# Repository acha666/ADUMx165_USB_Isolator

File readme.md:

# ADUMx165 USB Isolator

[Chinese Document / 中文文档](./readme.zh.md) | English Document

This is a USB 2.0 High-Speed (480Mbps) isolation module with an onboard 1-to-4 USB HUB, a 1A isolated DC-DC power supply, and support for external auxiliary power input with automatic switching between the two.

## Project Status

- [x] Schematic Design
- [x] PCB Design
- [x] PCB Fabrication
- [x] PCB Validation

## Device Overview

- **[ADUM3165](https://www.analog.com/en/products/adum3165.html)/[ADUM4165](https://www.analog.com/en/products/adum4165.html) USB Isolator**: Provides 480Mbps USB isolation with 3.75kV/5.7kV RMS isolation voltage. Pin-to-pin compatible.
- **[SN6505A](https://www.ti.com/product/SN6505A)/[B](https://www.ti.com/product/SN6505B) Transformer Driver**: An isolated DC-DC power controller powered directly from the upstream USB port. The two variants differ in switching frequency.
- **[DA2303-AL](https://www.coilcraft.com/en-us/products/transformers/power-transformers/isolation/da230x/da2303-al) Transformer**: 1:1.5 SMT transformer.
- **[TPS2116](https://www.ti.com/product/TPS2116) Power Multiplexer**: Prioritizes 5V auxiliary power from the downstream port. When unavailable, it automatically switches to the onboard isolated DC-DC power supply.
- **[TLV76701](https://www.ti.com/product/TLV767) LDO**: Regulates the output of the SN6505.
- **[CH334P](https://www.wch-ic.com/products/CH334.html) USB Hub**: A simple USB 2.0 1-to-4 HUB chip.

## Basic PCB Parameters

| Parameter               | Value                  |
|:-----------------------:|:----------------------:|
| **Dimensions**           | 50.00mm x 36.50mm     |
| **Shape**                | Rounded Rectangle, r=1.50mm |
| **Finished Thickness**   | 1.60mm                |
| **Copper Layers**        | 4                     |
| **Minimum Trace Width**  | 0.12mm                |
| **Minimum Trace Space**  | 0.12mm                |
| **Minimum Via Hole Diameter** | 0.20mm         |
| **Minimum Non-plated Hole Diameter** | >1.00mm |
| **Minimum Via Outer Diameter** | 0.45mm         |
| **Minimum Via Inner Diameter** | 0.20mm         |
| **Minimum Plated Slot Width** | 0.60mm          |
| **Minimum Non-plated Slot Width** | None        |
| **Special Manufacturing Processes** | Impedance Control |

## Impedance Control Parameters

### Differential Impedance 1

| Usage           | USB 2.0 Signals          |
|:---------------:|:------------------------:|
| **Signal Layers** | L1, L4                 |
| **Impedance**     | 90Ω                    |
| **Bottom Reference Layers** | L2, L3       |
| **Top Reference Layer** | None             |

| Current Design Parameters | Value            |
|:-------------------------:|:----------------:|
| **Trace Width**            | 0.12mm          |
| **Trace Spacing**          | 0.12mm          |
| **Copper Thickness**       | 1oz/0.5oz       |
| **Applicable PCB Stackup** | JLCPCB JLC04161H-3313 |

## Project Description

This project was designed using KiCad 8.06.

GitHub Action CI/CD is deployed, which automatically performs DRC checks and generates manufacturing files (e.g., Gerber files) with each commit.

Manufacturing files are available on the [Release Page](https://github.com/acha666/ADUMx165_USB_Isolator/releases) or the [Workflow](https://github.com/acha666/ADUMx165_USB_Isolator/actions/workflows/kicad-ci.yml).

### Power Design

The module includes a 1A onboard isolated DC-DC power supply and supports external auxiliary power input with automatic switching. The onboard LED indicates that the isolated-side 5V is provided by the onboard DC-DC power supply.

- When using a 5V external auxiliary power supply, the output ports prioritize this external power. The total output capacity depends on the external power supply. Each port is equipped with a self-recovering fuse, limiting current to 500mA.
- When no external power is connected, the onboard isolated DC-DC power supply generates 5V. The total output capacity is limited by both the isolated DC-DC power supply and the upstream USB port.

**Note**: The external auxiliary power supply must not be connected to the same device as the upstream USB port; otherwise, isolation will fail.

#### Updated Note (2024-12-15)

Previously, the TLV76750 was configured for a fixed 5V output. Under heavy load, line losses might reduce the output voltage. It has been replaced with the adjustable TLV76701, with the output voltage set to approximately 5.2V.

### Device Selection Recommendations

#### ADUM3165/4165

According to the [datasheet](https://www.analog.com/media/en/technical-documentation/data-sheets/adum3165-3166.pdf), both are pin-to-pin compatible. The main difference lies in the isolation voltage: 3.75kV for ADUM3165 and 5.7kV for ADUM4165. The test board uses ADUM3165.

#### SN6505A/B

SN6505A has a switching frequency of 160kHz, while SN6505B operates at 420kHz. The test board uses SN6505B.

Per the [datasheet, page 30](https://www.ti.com/lit/ds/sllsep9i/sllsep9i.pdf#page=30), both can be paired with the DA2303-AL transformer. However, SN6505A remains untested.

#### DA2303-AL

**Not recommended for substitution**, as it is optimized for SN6505A/B. Other models may require additional tuning.

#### Ferrite Beads (5 in total)

Based on the schematic, there are 0603 ferrite beads near the upstream input port and 0402 beads near the downstream USB ports (4 in total).

Ferrite beads are used to isolate power noise. Considering that USB ports may carry significant current under extreme conditions, their DC resistance (DCR) should be as low as possible to prevent overheating and voltage drops.

The test board uses the following components:

| Parameter\Model | BLM18SG121TN1D   | BLM15PX121SN1D   |
|:---------------:|:----------------:|:----------------:|
| Impedance       | 120Ω @ 100MHz    | 120Ω @ 100MHz    |
| Package Size    | 0603             | 0402             |
| DCR             | 25mΩ             | 55mΩ             |
| Rated Current   | 5A               | 3A               |

To reduce costs, ferrite beads can be replaced with 0Ω resistors.

#### Tantalum Capacitors

These prevent power instability on the isolated side during external power connection/disconnection. They can be omitted to save costs.

Tantalum capacitors are highly sensitive to overvoltage and polarity reversal, often failing catastrophically. It is recommended to select capacitors with a voltage rating at least twice the operating voltage (5V * 2 = 10V) and ensure correct polarity during soldering (the stripe mark typically indicates the positive terminal). This design uses 16V-rated tantalum capacitors.

### Notes

This document was translated by ChatGPT.

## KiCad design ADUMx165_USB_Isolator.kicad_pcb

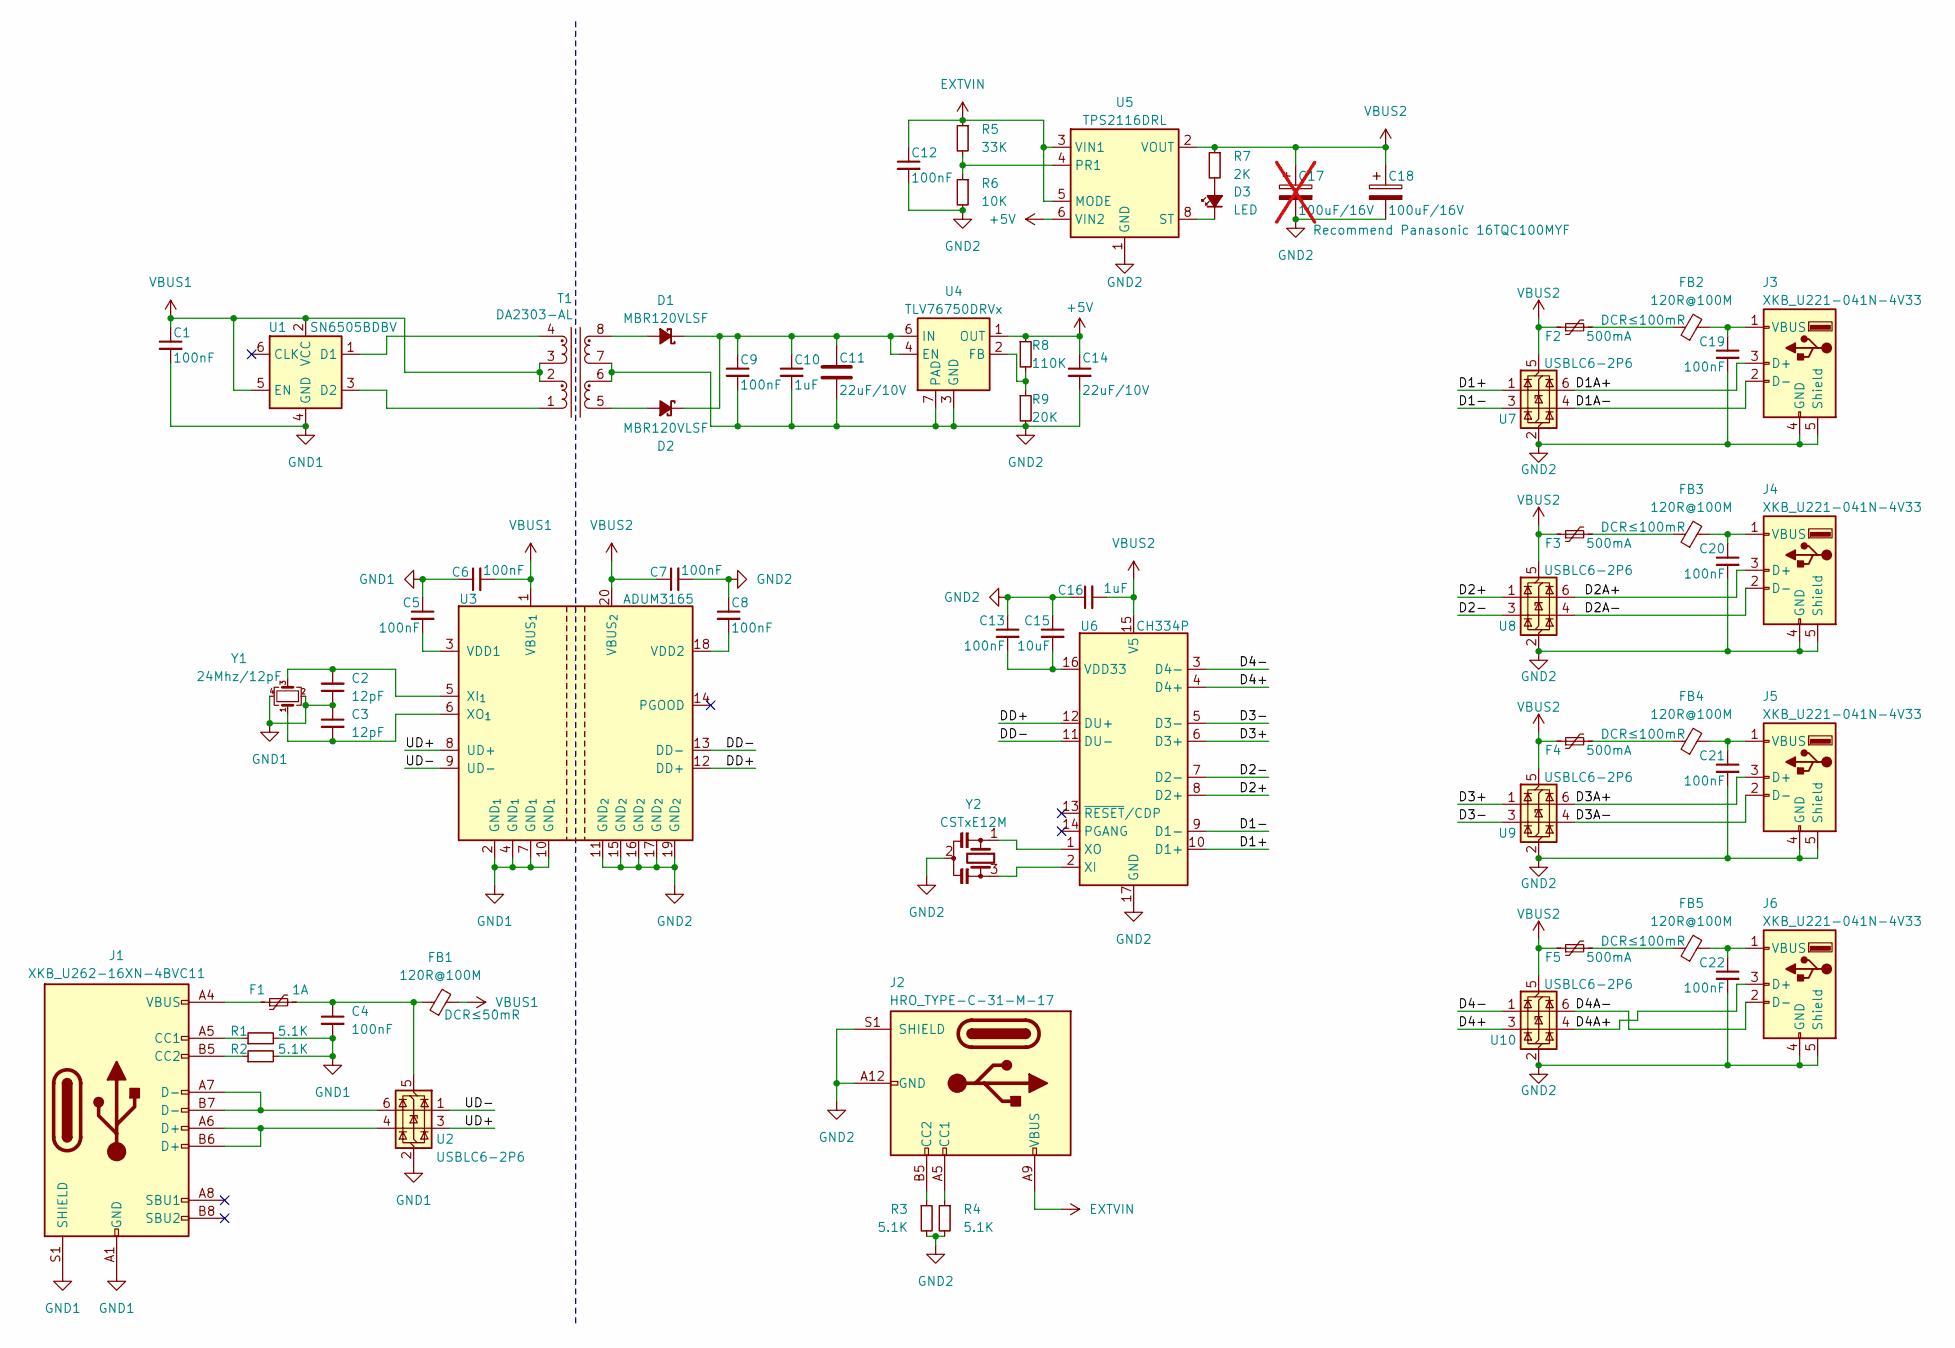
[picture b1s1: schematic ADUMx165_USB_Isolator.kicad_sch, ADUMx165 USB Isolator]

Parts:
C1, C4, C5, C6, C7, C8, C9, C12, C13, C19, C20, C21, C22: 100nF; C_0402_1005Metric
C2, C3: 12pF; C_0402_1005Metric
C10, C16: 1uF; C_0402_1005Metric
C11: 22uF/10V; C_0603_1608Metric
C14: 22uF/10V; C_0402_1005Metric
C15: 10uF; C_0402_1005Metric
C17: 100uF/16V; CP_EIA-7343-20_Kemet-V; not fitted
C18: 100uF/16V; CP_EIA-7343-20_Kemet-V
D1, D2: MBR120VLSF; D_SOD-123F
D3: LED; LED_0402_1005Metric
F1: 1A; Fuse_0603_1608Metric
F2, F3, F4, F5: 500mA; Fuse_0402_1005Metric
FB1: 120R@100M; L_0603_1608Metric
FB2, FB3, FB4, FB5: 120R@100M; L_0402_1005Metric
J1: XKB_U262-16XN-4BVC11; USB_C_Receptacle_XKB_U262-16XN-4BVC11
J2: HRO_TYPE-C-31-M-17; USB_C_Receptacle_HRO_TYPE-C-31-M-17
J3, J4, J5, J6: XKB_U221-041N-4V33; U221-041N-4V33
R1, R2, R3, R4: 5.1K; R_0402_1005Metric
R5: 33K; R_0402_1005Metric
R6: 10K; R_0402_1005Metric
R7: 2K; R_0402_1005Metric
R8: 110K; R_0402_1005Metric
R9: 20K; R_0402_1005Metric
T1: DA2303-AL
U1: SN6505BDBV; SOT-23-6
U2, U7, U8, U9, U10: USBLC6-2P6; SOT-666
U3: ADUM3165; SSOP-20_5.3x7.2mm_P0.65mm
U4: TLV76750DRVx; WSON-6-1EP_2x2mm_P0.65mm_EP1x1.6mm_ThermalVias
U5: TPS2116DRL; SOT-583-8
U6: CH334P; QFN-16-1EP_3x3mm_P0.5mm_EP1.75x1.75mm
Y1: 24Mhz/12pF; Crystal_SMD_2016-4Pin_2.0x1.6mm
Y2: CSTxE12M; Resonator_SMD_Murata_CSTxExxV-3Pin_3.0x1.1mm

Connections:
+5V: C14.1, R8.1, U4.1 (OUT), U5.6 (VIN2)
/D1+: U6.10 (D1+), U7.1 (I/O1)
/D1-: U6.9 (D1-), U7.3 (I/O2)
/D1A+: J3.3 (D+), U7.6 (I/O1)
/D1A-: J3.2 (D-), U7.4 (I/O2)
/D2+: U6.8 (D2+), U8.1 (I/O1)
/D2-: U6.7 (D2-), U8.3 (I/O2)
/D2A+: J4.3 (D+), U8.6 (I/O1)
/D2A-: J4.2 (D-), U8.4 (I/O2)
/D3+: U6.6 (D3+), U9.1 (I/O1)
/D3-: U6.5 (D3-), U9.3 (I/O2)
/D3A+: J5.3 (D+), U9.6 (I/O1)
/D3A-: J5.2 (D-), U9.4 (I/O2)
/D4+: U6.4 (D4+), U10.3 (I/O2)
/D4-: U6.3 (D4-), U10.1 (I/O1)
/D4A+: J6.3 (D+), U10.4 (I/O2)
/D4A-: J6.2 (D-), U10.6 (I/O1)
/DD+: U3.12 (DD+), U6.12 (DU+)
/DD-: U3.13 (DD-), U6.11 (DU-)
/UD+: U2.3 (I/O2), U3.8 (UD+)
/UD-: U2.1 (I/O1), U3.9 (UD-)
EXTVIN: C12.1, J2.A9 (VBUS), J2.B9 (VBUS), R5.1, U5.3 (VIN1), U5.5 (MODE)
GND1: C1.2, C2.1, C3.1, C4.2, C5.1, C6.1, J1.A1 (GND), J1.A12 (GND), J1.B1 (GND), J1.B12 (GND), J1.S1 (SHIELD), R1.2, R2.2, U1.4 (GND), U2.2 (GND), U3.2 (GND_{1}), U3.4 (GND_{1}), U3.7 (GND_{1}), U3.10 (GND_{1}), Y1.2, Y1.4
GND2: C7.2, C8.1, C9.2, C10.2, C11.2, C12.2, C13.1, C14.2, C15.1, C16.1, C17.2, C18.2, C19.2, C20.2, C21.2, C22.2, J2.A12 (GND), J2.B12 (GND), J2.S1 (SHIELD), J3.4 (GND), J3.5 (Shield), J4.4 (GND), J4.5 (Shield), J5.4 (GND), J5.5 (Shield), J6.4 (GND), J6.5 (Shield), R3.2, R4.2, R6.2, R9.2, T1.6 (OUT2A), T1.7 (OUT1B), U3.11 (GND_{2}), U3.15 (GND_{2}), U3.16 (GND_{2}), U3.17 (GND_{2}), U3.19 (GND_{2}), U4.3 (GND), U4.5 (GND), U4.7 (PAD), U5.1 (GND), U6.17 (GND), U7.2 (GND), U8.2 (GND), U9.2 (GND), U10.2 (GND), Y2.2
unnamed: D1.2 (A), T1.8 (OUT1A)
unnamed: C9.1, C10.1, C11.1, D1.1 (K), D2.1 (K), U4.4 (EN), U4.6 (IN)
unnamed: D2.2 (A), T1.5 (OUT2B)
unnamed: D3.2 (A), R7.2
unnamed: D3.1 (K), U5.8 (ST)
unnamed: F1.1, J1.A4 (VBUS), J1.A9 (VBUS), J1.B4 (VBUS), J1.B9 (VBUS)
unnamed: F2.2, FB2.1
unnamed: F3.2, FB3.1
unnamed: F4.2, FB4.1
unnamed: F5.2, FB5.1
unnamed: J1.A5 (CC1), R1.1
unnamed: J1.B5 (CC2), R2.1
unnamed: J1.A6 (D+), J1.B6 (D+), U2.4 (I/O2)
unnamed: J1.A7 (D-), J1.B7 (D-), U2.6 (I/O1)
unnamed: J2.A5 (CC1), R4.1
unnamed: J2.B5 (CC2), R3.1
unnamed: C19.1, FB2.2, J3.1 (VBUS)
unnamed: C20.1, FB3.2, J4.1 (VBUS)
unnamed: C21.1, FB4.2, J5.1 (VBUS)
unnamed: C22.1, FB5.2, J6.1 (VBUS)
unnamed: T1.4 (OUT1A), U1.1 (D1)
unnamed: T1.1 (OUT2B), U1.3 (D2)
unnamed: C4.1, F1.2, FB1.1, U2.5 (VBUS)
unnamed: C5.2, U3.3 (VDD1)
unnamed: C8.2, U3.18 (VDD2)
unnamed: C2.2, U3.5 (XI_{1}), Y1.3
unnamed: C3.2, U3.6 (XO_{1}), Y1.1
unnamed: R8.2, R9.1, U4.2 (FB)
unnamed: R5.2, R6.1, U5.4 (PR1)
unnamed: C13.2, C15.2, U6.16 (VDD33)
unnamed: U6.2 (XI), Y2.3
unnamed: U6.1 (XO), Y2.1
VBUS1: C1.1, C6.2, FB1.2, T1.2 (OUT2A), T1.3 (OUT1B), U1.2 (VCC), U1.5 (EN), U3.1 (VBUS_{1})
VBUS2: C7.1, C16.2, C17.1, C18.1, F2.1, F3.1, F4.1, F5.1, R7.1, U3.20 (VBUS_{2}), U5.2 (VOUT), U5.7 (VOUT), U6.15 (V5), U7.5 (VBUS), U8.5 (VBUS), U9.5 (VBUS), U10.5 (VBUS)

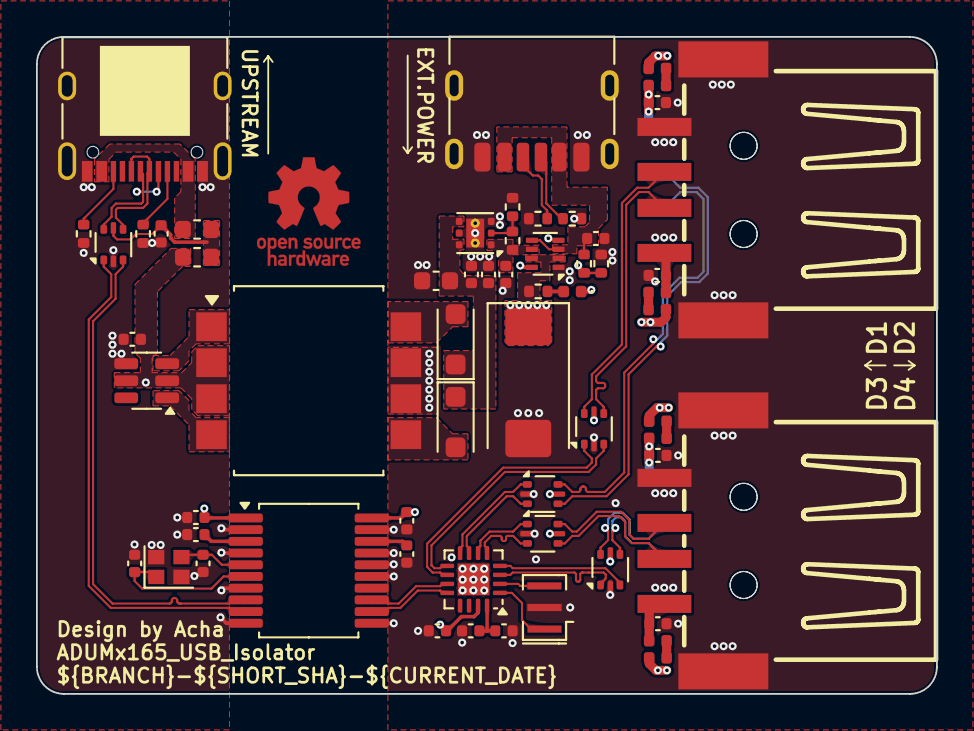
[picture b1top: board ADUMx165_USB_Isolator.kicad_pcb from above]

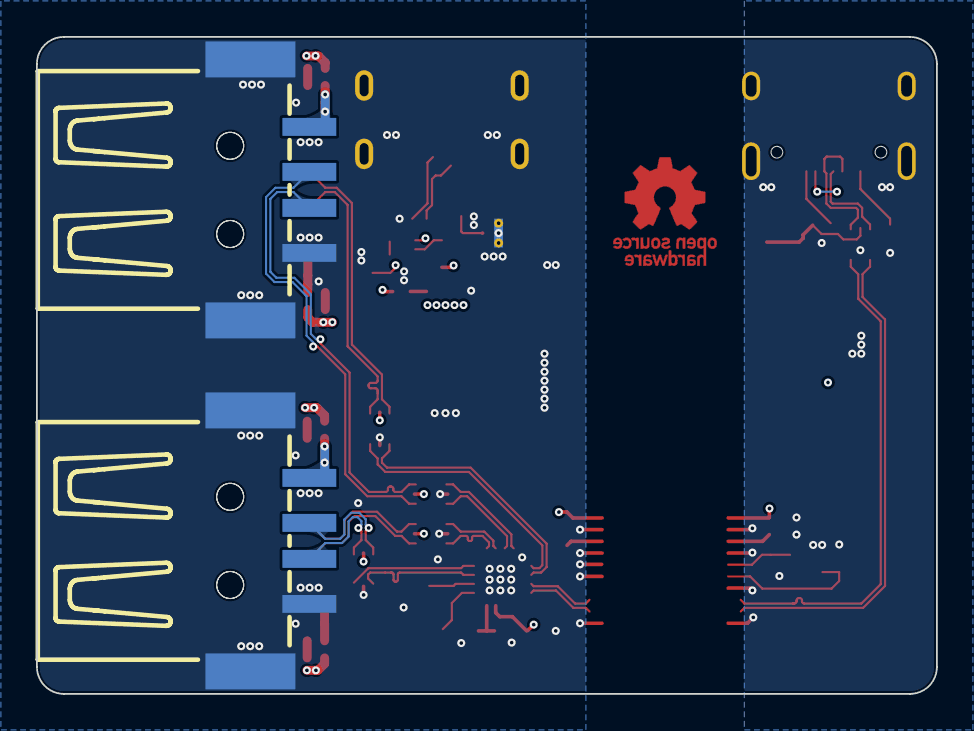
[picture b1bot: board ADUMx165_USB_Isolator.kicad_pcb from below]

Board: 4 copper layers, 50.0 x 36.5 mm, 62 parts (2 on the bottom side), 58 nets.

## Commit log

2024-11-15 Update workflow Embed 3D models Board shape & silkscreen change
2024-11-15 Update workflow
2024-11-15 Update workflow PCB text objects changes
2024-11-15 Fix typo
2024-11-17 Add GND Vias Update Workflow
2024-11-17 Update FuckJLC
2024-11-18 Change drill file export format
2024-11-30 Update readme.md Add Eng translation Add board image Change R7 value to 2K
2024-11-30 Fix readme image issue
2024-11-30 Fix readme link issue
2024-12-15 Change TLV76750 to TLV76701
2025-01-05 Upd brd img
